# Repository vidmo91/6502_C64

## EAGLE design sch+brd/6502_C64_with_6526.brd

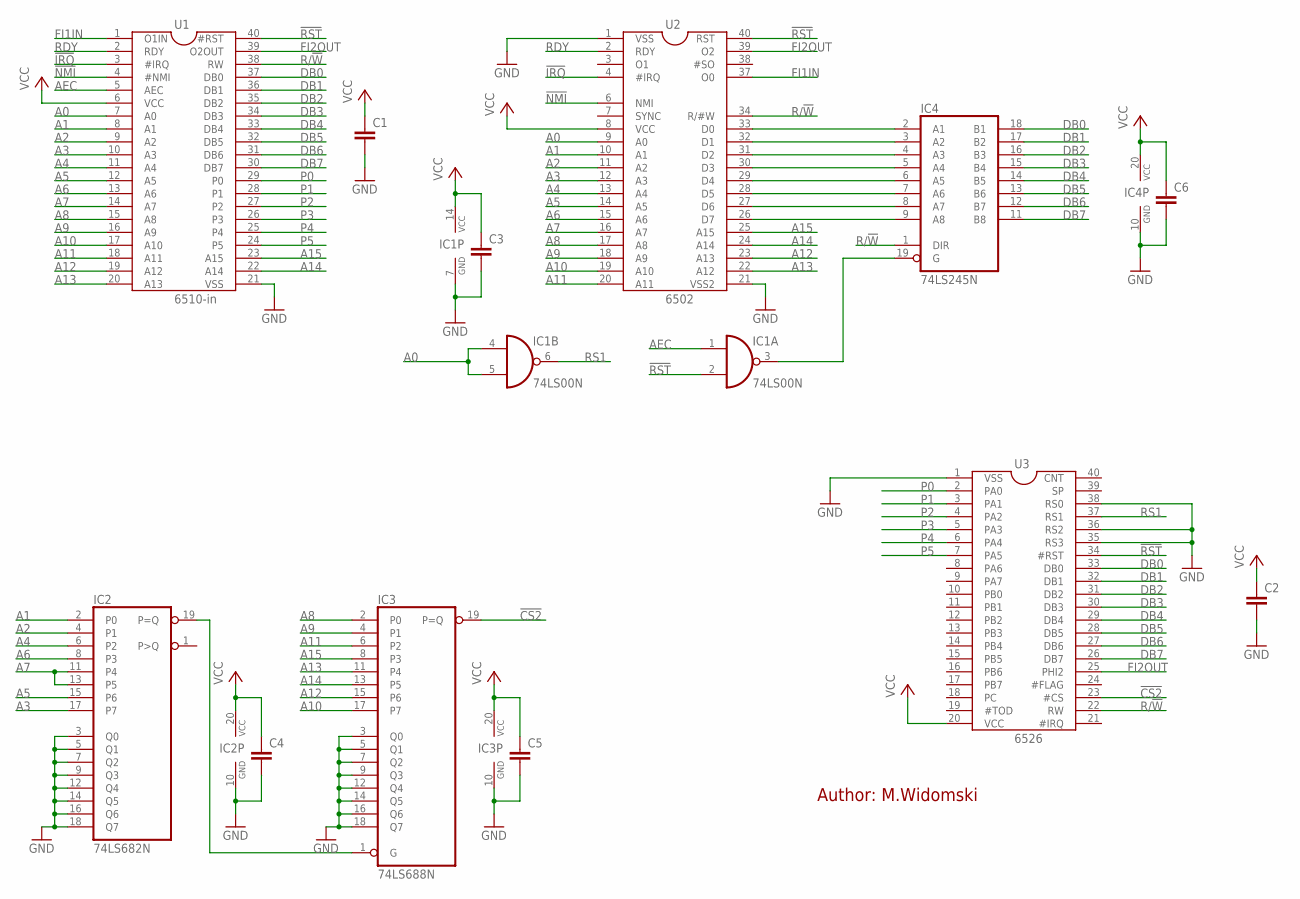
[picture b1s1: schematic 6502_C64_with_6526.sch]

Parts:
C1, C2, C3, C4, C5, C6: C-EU025-025X050; C025-025X050
IC1: 74LS00N; DIL14
IC2: 74LS682N; DIL20
IC3: 74LS688N; DIL20
IC4: 74LS245N; DIL20
U1: 6510-in; DIL40
U2: 6502; DIL40
U3: 6526; DIL40

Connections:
!CS2: IC3.19 (P=Q), U3.23 (#CS)
!IRQ: U1.3 (#IRQ), U2.4 (#IRQ)
!NMI: U1.4 (#NMI), U2.6 (NMI)
!RST: IC1.2 (I1), U1.40 (#RST), U2.40 (RST), U3.34 (#RST)
A0: IC1.4 (I0), IC1.5 (I1), U1.7 (A0), U2.9 (A0)
A1: IC2.2 (P0), U1.8 (A1), U2.10 (A1)
A2: IC2.4 (P1), U1.9 (A2), U2.11 (A2)
A3: IC2.17 (P7), U1.10 (A3), U2.12 (A3)
A4: IC2.6 (P2), U1.11 (A4), U2.13 (A4)
A5: IC2.15 (P6), U1.12 (A5), U2.14 (A5)
A6: IC2.8 (P3), U1.13 (A6), U2.15 (A6)
A7: IC2.11 (P4), IC2.13 (P5), U1.14 (A7), U2.16 (A7)
A8: IC3.2 (P0), U1.15 (A8), U2.17 (A8)
A9: IC3.4 (P1), U1.16 (A9), U2.18 (A9)
A10: IC3.17 (P7), U1.17 (A10), U2.19 (A10)
A11: IC3.6 (P2), U1.18 (A11), U2.20 (A11)
A12: IC3.15 (P6), U1.19 (A12), U2.23 (A13)
A13: IC3.11 (P4), U1.20 (A13), U2.22 (A12)
A14: IC3.13 (P5), U1.22 (A14), U2.24 (A14)
A15: IC3.8 (P3), U1.23 (A15), U2.25 (A15)
AEC: IC1.1 (I0), U1.5 (AEC)
DB0: IC4.18 (B1), U1.37 (DB0), U3.33 (DB0)
DB1: IC4.17 (B2), U1.36 (DB1), U3.32 (DB1)
DB2: IC4.16 (B3), U1.35 (DB2), U3.31 (DB2)
DB3: IC4.15 (B4), U1.34 (DB3), U3.30 (DB3)
DB4: IC4.14 (B5), U1.33 (DB4), U3.29 (DB4)
DB5: IC4.13 (B6), U1.32 (DB5), U3.28 (DB5)
DB6: IC4.12 (B7), U1.31 (DB6), U3.27 (DB6)
DB7: IC4.11 (B8), U1.30 (DB7), U3.26 (DB7)
FI1IN: U1.1 (O1IN), U2.37 (O0)
FI2OUT: U1.39 (O2OUT), U2.39 (O2), U3.25 (PHI2)
GND: C1.2, C2.2, C3.2, C4.2, C5.2, C6.2, IC1.7 (GND), IC2.3 (Q0), IC2.5 (Q1), IC2.7 (Q2), IC2.9 (Q3), IC2.10 (GND), IC2.12 (Q4), IC2.14 (Q5), IC2.16 (Q6), IC2.18 (Q7), IC3.3 (Q0), IC3.5 (Q1), IC3.7 (Q2), IC3.9 (Q3), IC3.10 (GND), IC3.12 (Q4), IC3.14 (Q5), IC3.16 (Q6), IC3.18 (Q7), IC4.10 (GND), U1.21 (VSS), U2.1 (VSS), U2.21 (VSS2), U3.1 (VSS), U3.35 (RS3), U3.36 (RS2), U3.38 (RS0)
unnamed: IC4.2 (A1), U2.33 (D0)
unnamed: IC4.3 (A2), U2.32 (D1)
unnamed: IC4.4 (A3), U2.31 (D2)
unnamed: IC4.5 (A4), U2.30 (D3)
unnamed: IC4.6 (A5), U2.29 (D4)
unnamed: IC4.7 (A6), U2.28 (D5)
unnamed: IC4.8 (A7), U2.27 (D6)
unnamed: IC4.9 (A8), U2.26 (D7)
unnamed: IC1.3 (O), IC4.19 (G)
unnamed: IC2.19 (P=Q), IC3.1 (G)
P0: U1.29 (P0), U3.2 (PA0)
P1: U1.28 (P1), U3.3 (PA1)
P2: U1.27 (P2), U3.4 (PA2)
P3: U1.26 (P3), U3.5 (PA3)
P4: U1.25 (P4), U3.6 (PA4)
P5: U1.24 (P5), U3.7 (PA5)
R/!W: IC4.1 (DIR), U1.38 (RW), U2.34 (R/#W), U3.22 (RW)
RDY: U1.2 (RDY), U2.2 (RDY)
RS1: IC1.6 (O), U3.37 (RS1)
VCC: C1.1, C2.1, C3.1, C4.1, C5.1, C6.1, IC1.14 (VCC), IC2.20 (VCC), IC3.20 (VCC), IC4.20 (VCC), U1.6 (VCC), U2.8 (VCC), U3.20 (VCC)

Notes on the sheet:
Author: M.Widomski

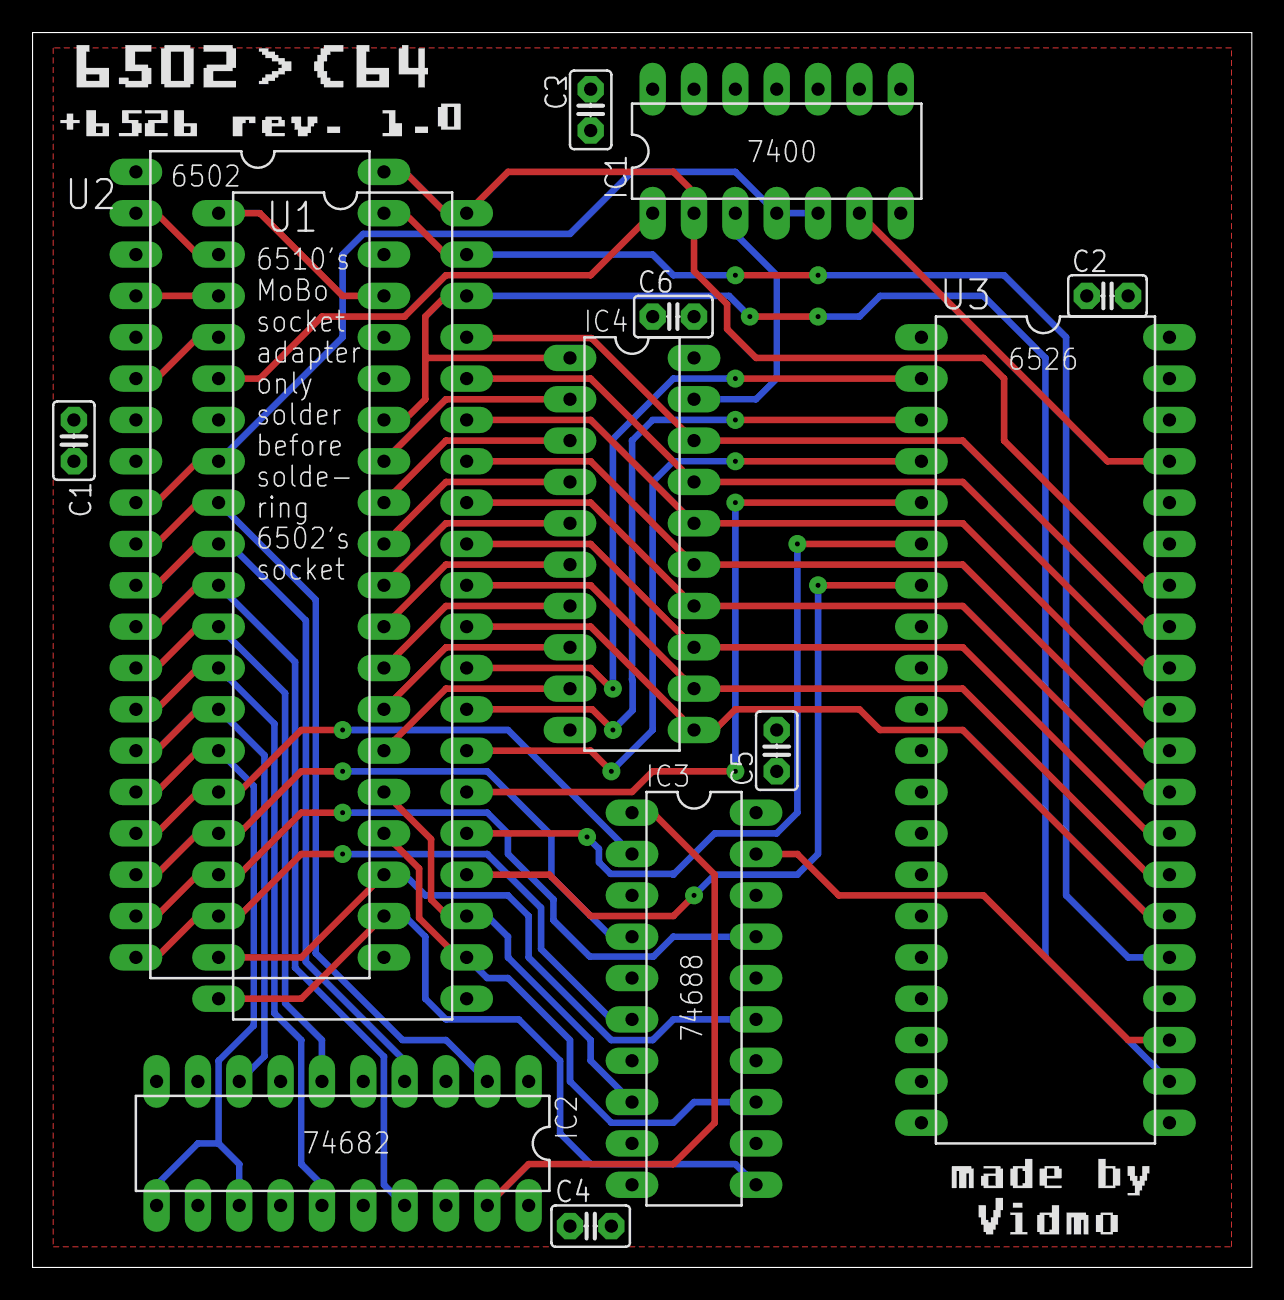
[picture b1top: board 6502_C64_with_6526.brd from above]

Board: 2 copper layers, 74.9 x 75.9 mm, 13 parts (0 on the bottom side), 52 nets.

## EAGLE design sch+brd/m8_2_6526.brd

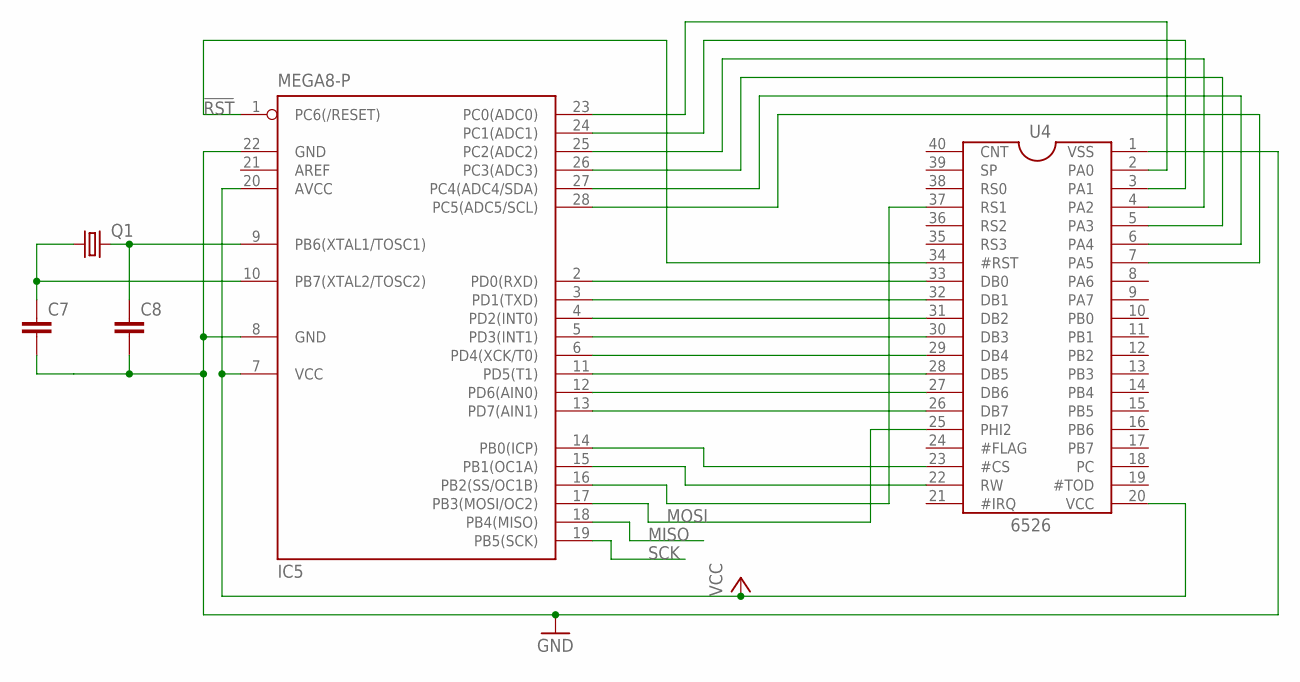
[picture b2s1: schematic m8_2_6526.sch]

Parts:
C7, C8: C-EU025-025X050; C025-025X050
IC5: MEGA8-P; DIL28-3
Q1: CRYSTALHC49S; HC49/S
U4: 6526; DIL40

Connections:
!RST: IC5.1 (PC6(/RESET)), U4.34 (#RST)
GND: C7.2, C8.2, IC5.8 (GND), IC5.22 (GND), U4.1 (VSS)
MISO: IC5.18 (PB4(MISO))
MOSI: IC5.17 (PB3(MOSI/OC2)), U4.25 (PHI2)
unnamed: IC5.2 (PD0(RXD)), U4.33 (DB0)
unnamed: IC5.3 (PD1(TXD)), U4.32 (DB1)
unnamed: IC5.4 (PD2(INT0)), U4.31 (DB2)
unnamed: IC5.5 (PD3(INT1)), U4.30 (DB3)
unnamed: IC5.6 (PD4(XCK/T0)), U4.29 (DB4)
unnamed: IC5.11 (PD5(T1)), U4.28 (DB5)
unnamed: IC5.12 (PD6(AIN0)), U4.27 (DB6)
unnamed: IC5.13 (PD7(AIN1)), U4.26 (DB7)
unnamed: IC5.23 (PC0(ADC0)), U4.2 (PA0)
unnamed: IC5.24 (PC1(ADC1)), U4.3 (PA1)
unnamed: IC5.25 (PC2(ADC2)), U4.4 (PA2)
unnamed: IC5.26 (PC3(ADC3)), U4.5 (PA3)
unnamed: IC5.27 (PC4(ADC4/SDA)), U4.6 (PA4)
unnamed: IC5.28 (PC5(ADC5/SCL)), U4.7 (PA5)
unnamed: IC5.14 (PB0(ICP)), U4.23 (#CS)
unnamed: IC5.15 (PB1(OC1A)), U4.22 (RW)
unnamed: IC5.16 (PB2(SS/OC1B)), U4.37 (RS1)
unnamed: C8.1, IC5.9 (PB6(XTAL1/TOSC1)), Q1.2
unnamed: C7.1, IC5.10 (PB7(XTAL2/TOSC2)), Q1.1
SCK: IC5.19 (PB5(SCK))
VCC: IC5.7 (VCC), IC5.20 (AVCC), U4.20 (VCC)

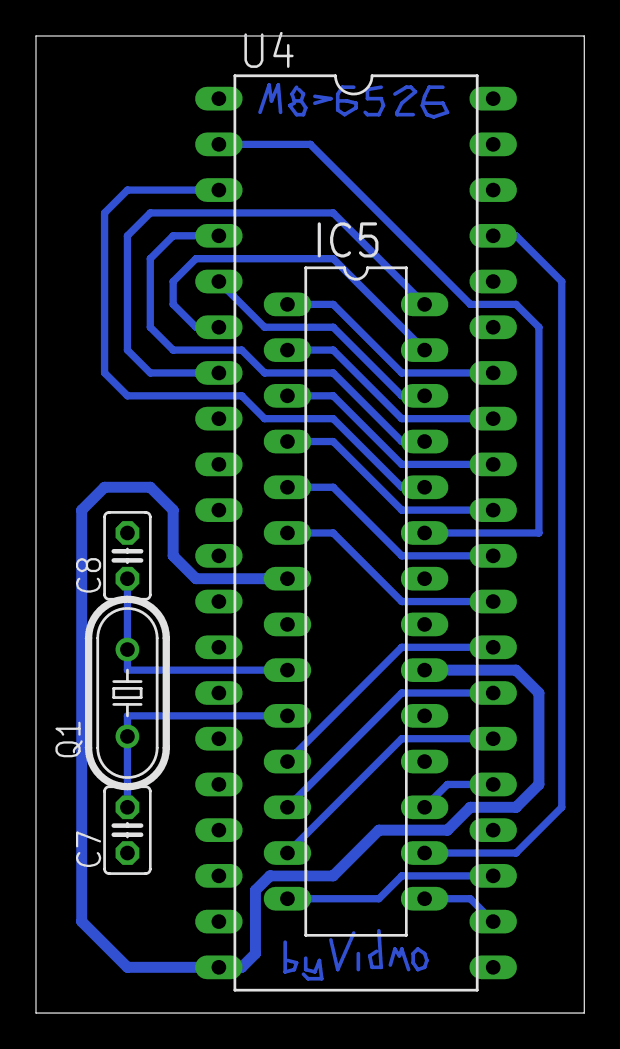
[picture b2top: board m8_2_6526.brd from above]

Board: 2 copper layers, 30.5 x 54.3 mm, 5 parts (0 on the bottom side), 23 nets.
